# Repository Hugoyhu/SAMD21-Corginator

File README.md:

# SAMD21-Corginator

The Corginator _v2_ is an updated version of the original Corginator (which had an ATMEGA328P microcontroller). Here's what's new:
* ATMega328P replaced with ATSAMD21G18 (faster, more memory, more storage, and more bits!)
* ICSP programming replaced with keyed SWD header 
* Bulky USB Type-B replaced with USB Type-C connector
* Arduino Nano form factor replaced with Adafruit Feather form factor
* Li-poly single cell battery charging enabled with Microchip MCP73831
* Smaller and lighter design

___CHECK BATTERY PINOUT FIRST. POLARITY MAY BE REVERSED.___
# Open Source Hardware

The Corginator v2 is open source hardware. This design was created in [KiCAD](https://www.kicad.org), an FOSS schematic capture and PCB layout / routing software. While schematics are provided in PDF format, you will need the latest version of KiCAD (v8 or above) to directly view and modify the schematic and PCB. 

## Schematic

## PCB 

# Attribution 

This design uses the [Adafruit Feather M0](https://www.adafruit.com/product/2772) as a reference design for both the SAMD21 and battery charging. I also used their [wonderful tutorial](https://learn.adafruit.com/how-to-program-samd-bootloaders/overview) to flash a bootloader onto the Corginator with my Segger J-link EDU. 

To support Adafruit's open-source hardware _and_ software development, please consider using their USA-designed & manufacturered products in your next project.

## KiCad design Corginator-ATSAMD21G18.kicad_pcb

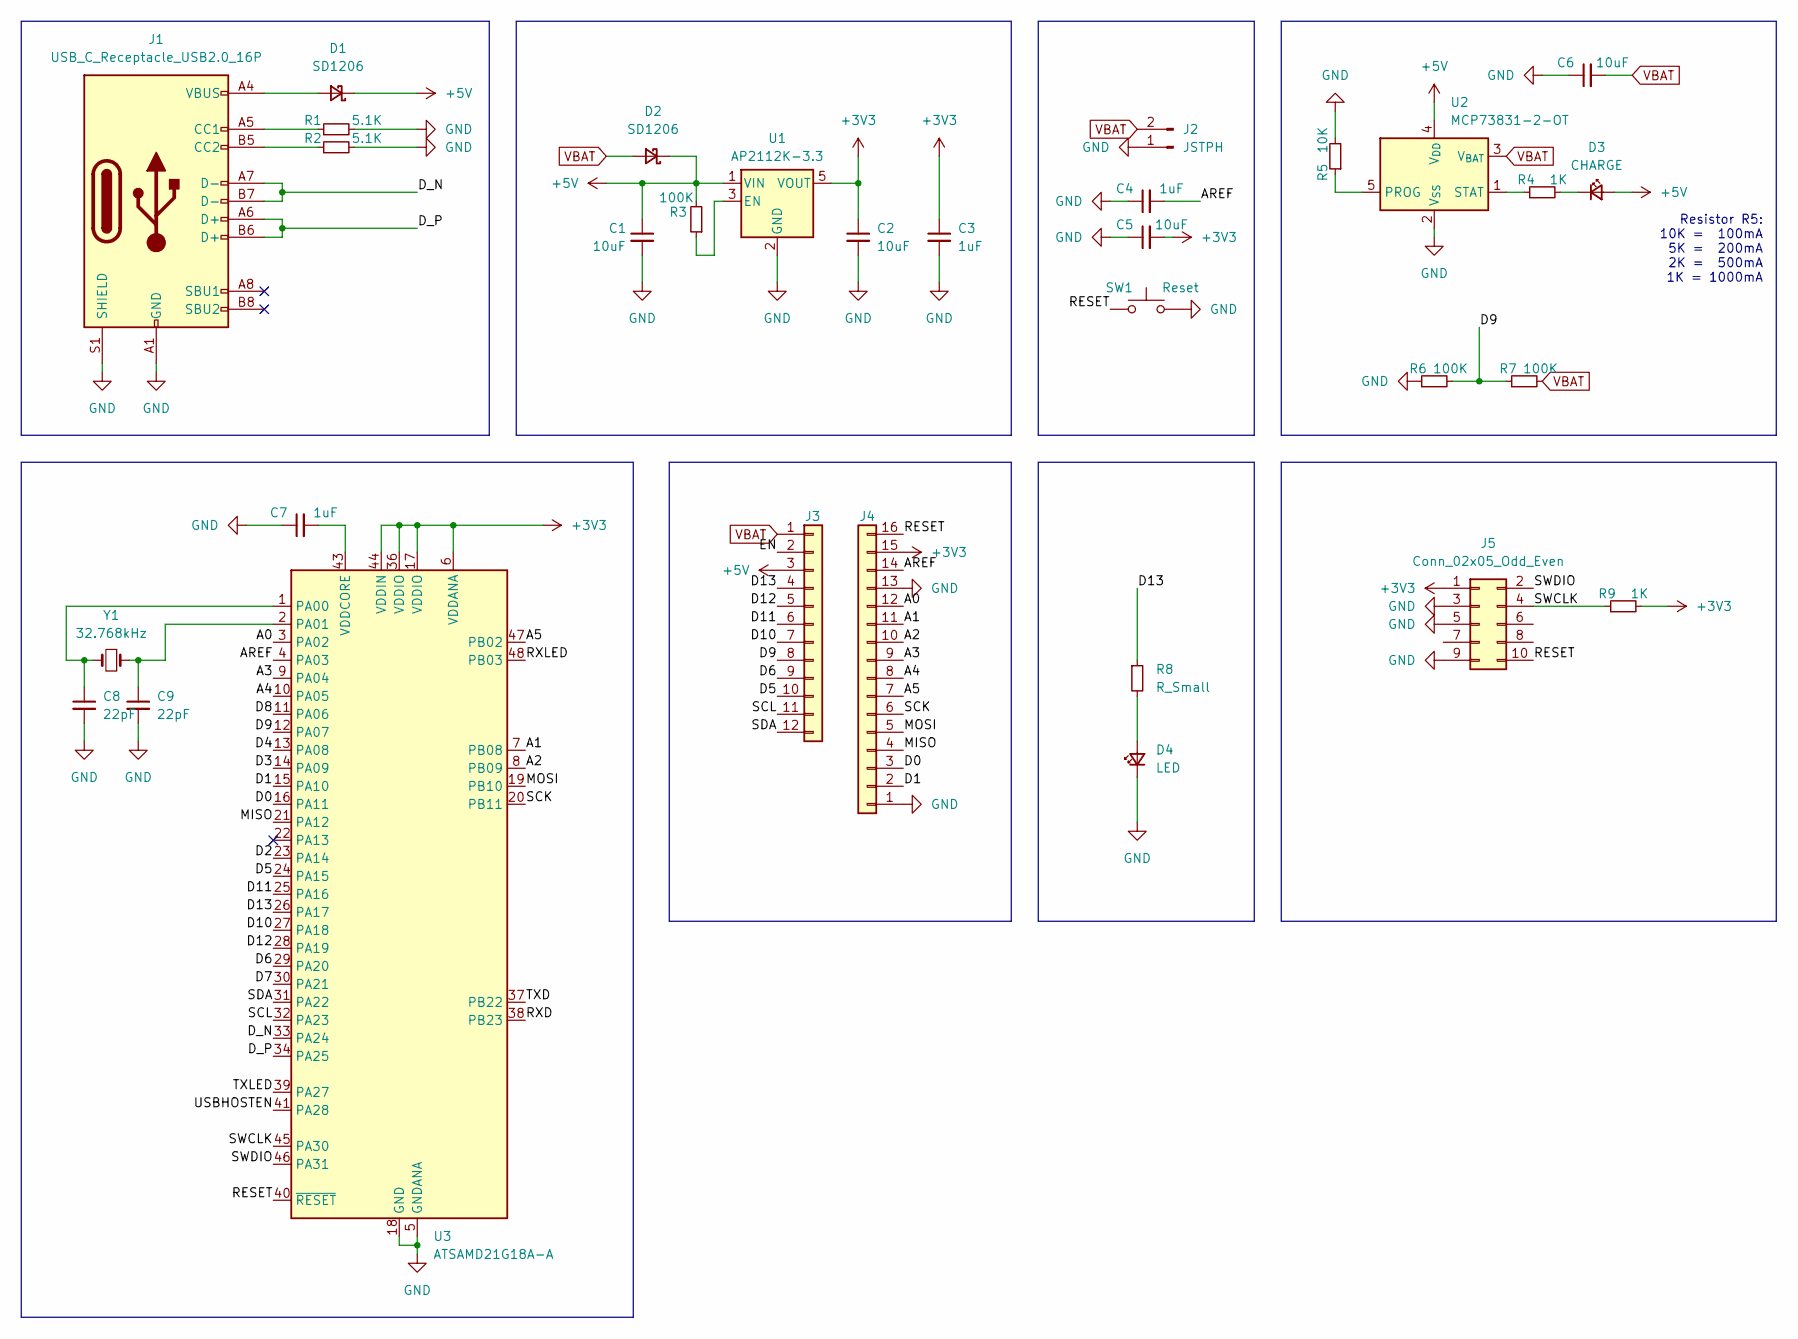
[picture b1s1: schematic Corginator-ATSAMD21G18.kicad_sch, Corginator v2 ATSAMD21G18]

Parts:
C1, C2, C5, C6: 10uF; C_0603_1608Metric_Pad1.08x0.95mm_HandSolder
C3, C4, C7: 1uF; C_0603_1608Metric_Pad1.08x0.95mm_HandSolder
C8, C9: 22pF; C_0603_1608Metric_Pad1.08x0.95mm_HandSolder
D1, D2: SD1206; D_1206_3216Metric_Pad1.42x1.75mm_HandSolder
D3: CHARGE; LED_0603_1608Metric_Pad1.05x0.95mm_HandSolder
D4: LED; LED_0805_2012Metric_Pad1.15x1.40mm_HandSolder
J1: USB_C_Receptacle_USB2.0_16P; USB_C_Receptacle_HRO_TYPE-C-31-M-12
J2: JSTPH; JST_PH_B2B-PH-SM4-TB_1x02-1MP_P2.00mm_Vertical
J3: Conn_01x12; PinSocket_1x12_P2.54mm_Vertical
J4: Conn_01x16; PinSocket_1x16_P2.54mm_Vertical
J5: Conn_02x05_Odd_Even; PinHeader_2x05_P1.27mm_Vertical
R1, R2: 5.1K; R_0603_1608Metric_Pad0.98x0.95mm_HandSolder
R3, R6, R7: 100K; R_0603_1608Metric_Pad0.98x0.95mm_HandSolder
R4, R9: 1K; R_0603_1608Metric_Pad0.98x0.95mm_HandSolder
R5: 10K; R_0603_1608Metric_Pad0.98x0.95mm_HandSolder
R8: R_Small; R_0603_1608Metric_Pad0.98x0.95mm_HandSolder
SW1: Reset; SW_SPST_PTS645
U1: AP2112K-3.3; SOT-23-5
U2: MCP73831-2-OT; SOT-23-5
U3: ATSAMD21G18A-A; TQFP-48_7x7mm_P0.5mm
Y1: 32.768kHz; Crystal_Round_D3.0mm_Vertical

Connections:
+3V3: C2.1, C3.1, C5.2, J4.15, J5.1, R9.2, U1.5 (VOUT), U3.6 (VDDANA), U3.17 (VDDIO), U3.36 (VDDIO), U3.44 (VDDIN)
+5V: C1.1, D1.1 (K), D2.1 (K), D3.2 (A), J3.3, R3.2, U1.1 (VIN), U2.4 (V_{DD})
/A0: J4.12, U3.3 (PA02)
/A1: J4.11, U3.7 (PB08)
/A2: J4.10, U3.8 (PB09)
/A3: J4.9, U3.9 (PA04)
/A4: J4.8, U3.10 (PA05)
/A5: J4.7, U3.47 (PB02)
/AREF: C4.2, J4.14, U3.4 (PA03)
/D0: J4.3, U3.16 (PA11)
/D1: J4.2, U3.15 (PA10)
/D2: U3.23 (PA14)
/D3: U3.14 (PA09)
/D4: U3.13 (PA08)
/D5: J3.10, U3.24 (PA15)
/D6: J3.9, U3.29 (PA20)
/D7: U3.30 (PA21)
/D8: U3.11 (PA06)
/D9: J3.8, R6.2, R7.1, U3.12 (PA07)
/D10: J3.7, U3.27 (PA18)
/D11: J3.6, U3.25 (PA16)
/D12: J3.5, U3.28 (PA19)
/D13: J3.4, R8.1, U3.26 (PA17)
/D_N: J1.A7 (D-), J1.B7 (D-), U3.33 (PA24)
/D_P: J1.A6 (D+), J1.B6 (D+), U3.34 (PA25)
/EN: J3.2
/MISO: J4.4, U3.21 (PA12)
/MOSI: J4.5, U3.19 (PB10)
/RESET: J4.16, J5.10, SW1.1, U3.40 (~RESET)
/RXD: U3.38 (PB23)
/RXLED: U3.48 (PB03)
/SCK: J4.6, U3.20 (PB11)
/SCL: J3.11, U3.32 (PA23)
/SDA: J3.12, U3.31 (PA22)
/SWCLK: J5.4, R9.1, U3.45 (PA30)
/SWDIO: J5.2, U3.46 (PA31)
/TXD: U3.37 (PB22)
/TXLED: U3.39 (PA27)
/USBHOSTEN: U3.41 (PA28)
GND: C1.2, C2.2, C3.2, C4.1, C5.1, C6.1, C7.1, C8.2, C9.2, D4.1 (K), J1.A1 (GND), J1.A12 (GND), J1.B1 (GND), J1.B12 (GND), J1.S1 (SHIELD), J2.1, J4.1, J4.13, J5.3, J5.5, J5.9, R1.2, R2.2, R5.2, R6.1, SW1.2, U1.2 (GND), U2.2 (V_{SS}), U3.5 (GNDANA), U3.18 (GND), U3.35 (GND), U3.42 (GND)
unnamed: D1.2 (A), J1.A4 (VBUS), J1.A9 (VBUS), J1.B4 (VBUS), J1.B9 (VBUS)
unnamed: D3.1 (K), R4.2
unnamed: D4.2 (A), R8.2
unnamed: J1.A5 (CC1), R1.1
unnamed: J1.B5 (CC2), R2.1
unnamed: R3.1, U1.3 (EN)
unnamed: R5.1, U2.5 (PROG)
unnamed: R4.1, U2.1 (STAT)
unnamed: C8.1, U3.1 (PA00), Y1.2
unnamed: C9.1, U3.2 (PA01), Y1.1
unnamed: C7.2, U3.43 (VDDCORE)
VBAT: C6.2, D2.2 (A), J2.2, J3.1, R7.2, U2.3 (V_{BAT})

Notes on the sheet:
Resistor R5: 10K = 100mA 5K = 200mA 2K = 500mA 1K = 1000mA

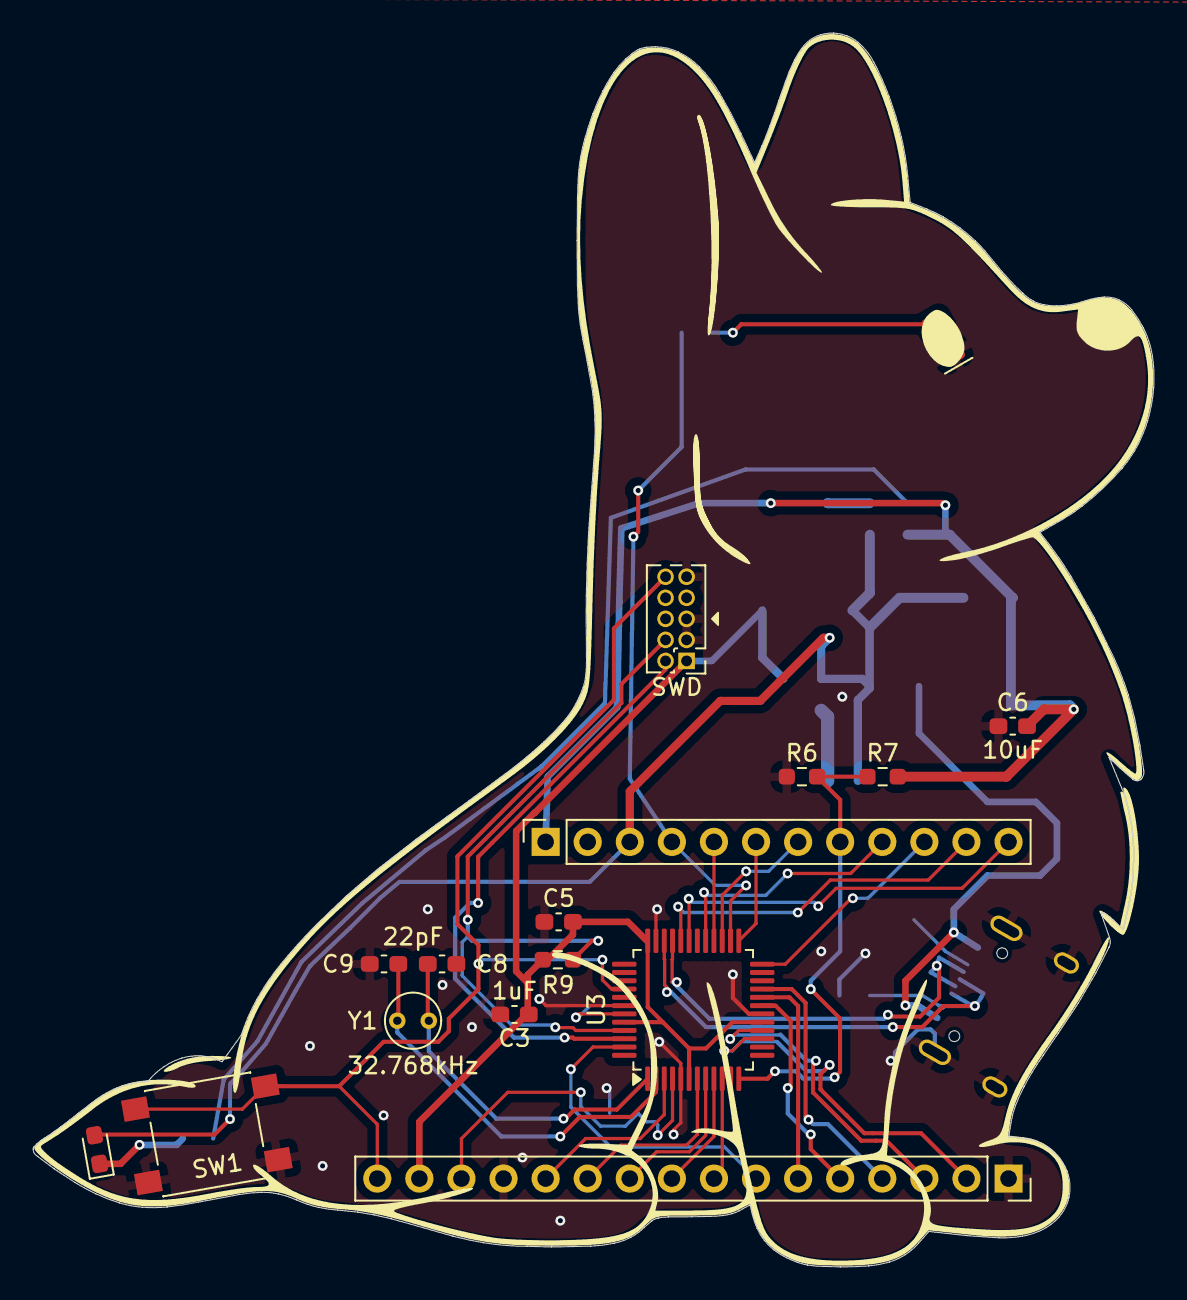
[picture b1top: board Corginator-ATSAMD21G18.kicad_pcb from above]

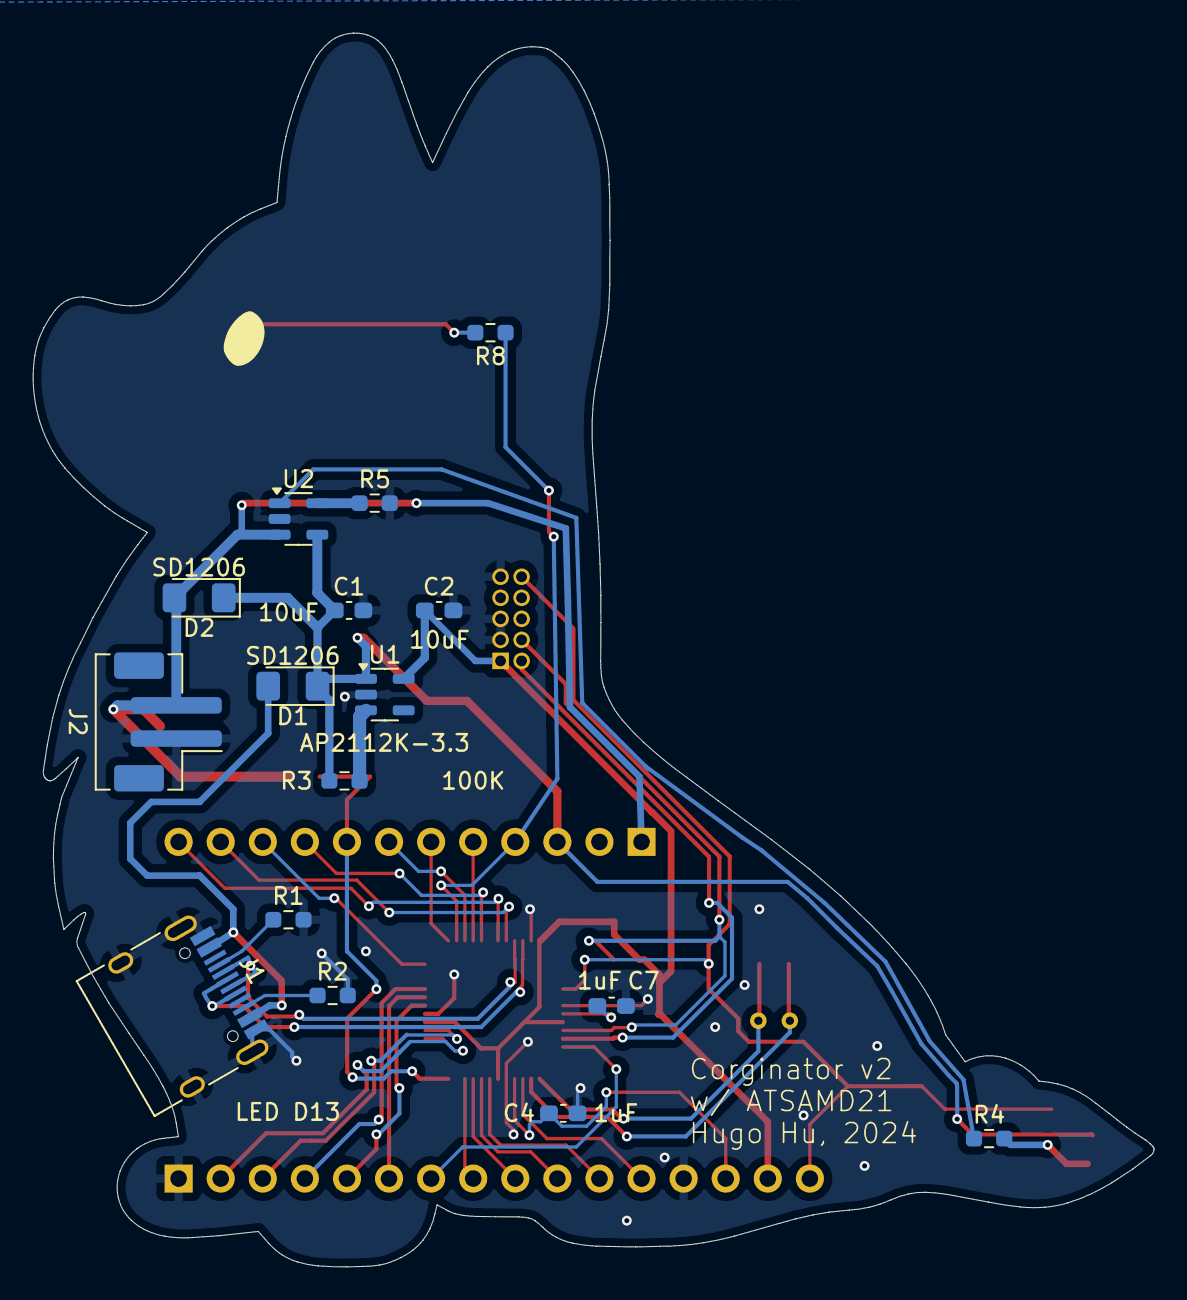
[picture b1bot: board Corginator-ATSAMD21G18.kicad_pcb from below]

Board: 2 copper layers, 67.7 x 74.5 mm, 32 parts (16 on the bottom side), 41 nets.

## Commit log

2024-08-10 add kicad files
2024-08-10 Add files via upload
    update for consistency
2024-08-10 add pdf
